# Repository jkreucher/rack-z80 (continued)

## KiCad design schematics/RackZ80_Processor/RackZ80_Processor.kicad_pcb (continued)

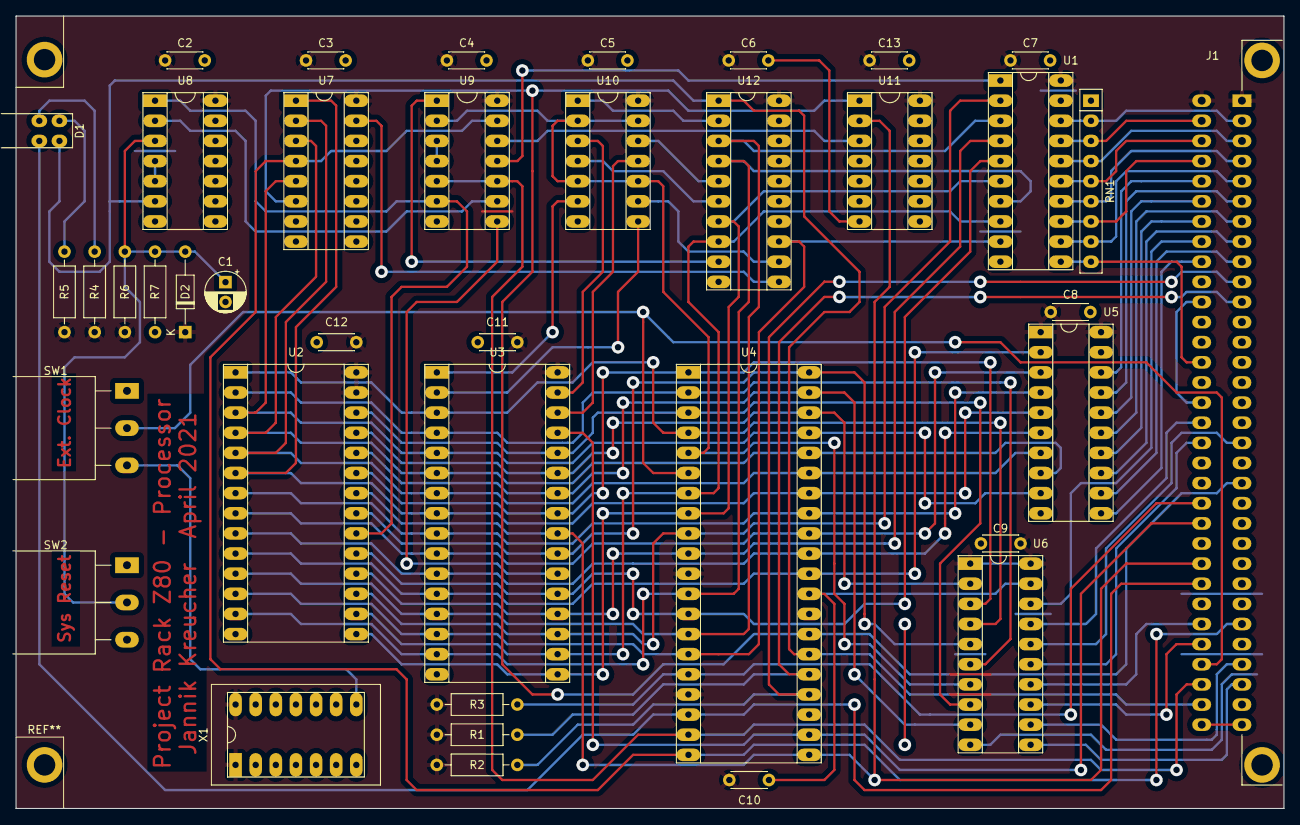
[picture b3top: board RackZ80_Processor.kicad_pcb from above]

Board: 2 copper layers, 160.0 x 100.0 mm, 39 parts (0 on the bottom side), 83 nets.

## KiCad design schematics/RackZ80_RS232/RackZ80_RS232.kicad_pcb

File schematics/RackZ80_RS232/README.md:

# Serial I/O

Copyright 2021 Jannik Kreucher

## Table of Contents
 - [How it works](#how-it-works)
 - [Schematic](#schematic)

## How it works
TODO

## Schematic
The [schematic](documentation/RackZ80_RS232.pdf) exported as pdf. So it is ready to print.

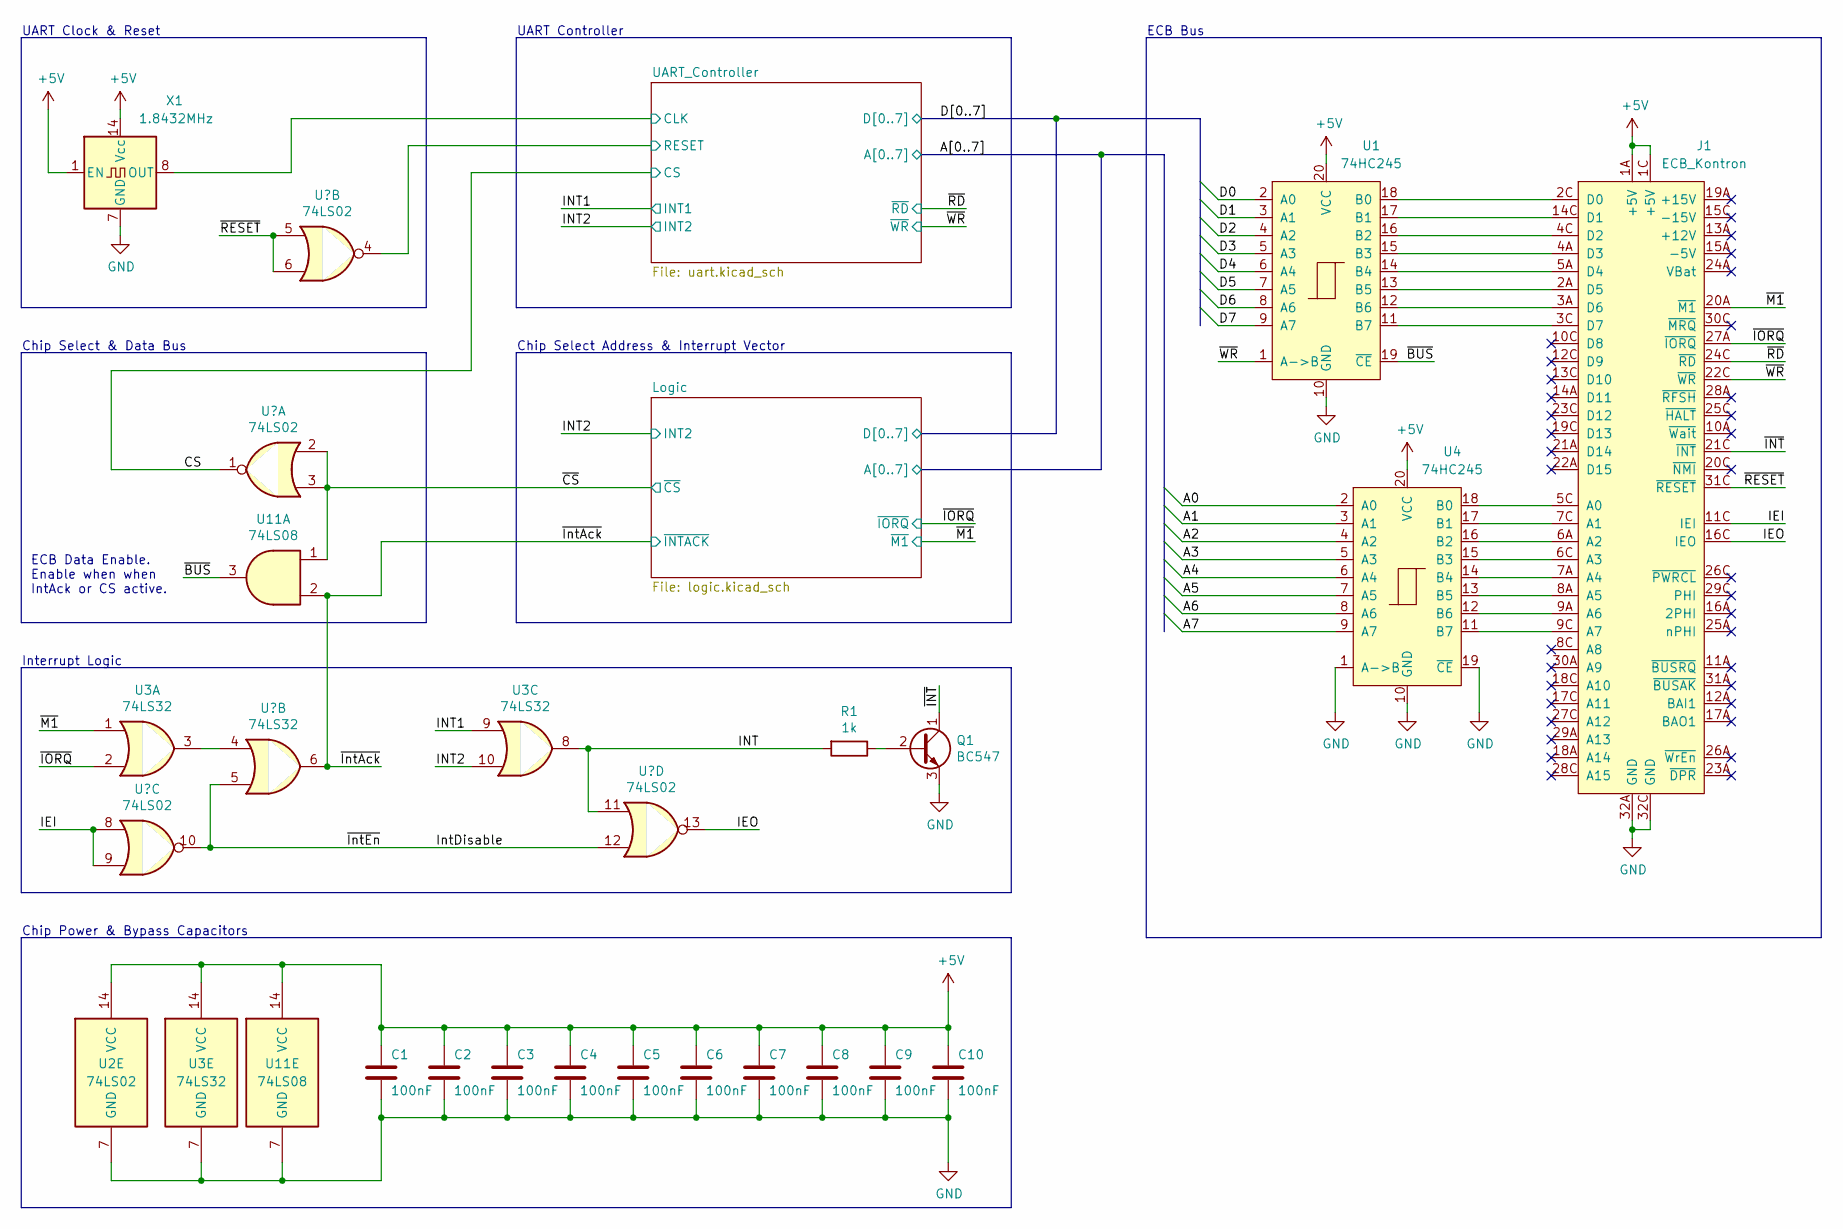
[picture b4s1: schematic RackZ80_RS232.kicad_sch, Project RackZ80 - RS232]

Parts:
C1, C2, C3, C4, C5, C6, C7, C8, C9, C10: 100nF; C_Disc_D4.3mm_W1.9mm_P5.00mm
J1: ECB_Kontron; Eurocard_DIN41612_C64_Male
Q1: BC547; TO-92S_Wide
R1: 1k; R_Axial_DIN0207_L6.3mm_D2.5mm_P10.16mm_Horizontal
U1, U4: 74HC245; DIP-20_Socket
U2: 74LS02; DIP-14_Socket
U3: 74LS32; DIP-14_Socket
U11: 74LS08; DIP-14_Socket
X1: 1.8432MHz; DIP-14_Oscillator_Socket

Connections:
+5V: C1.1, C2.1, C3.1, C4.1, C5.1, C6.1, C7.1, C8.1, C9.1, C10.1, J1.1A (+5V), J1.1C (+5V), U1.20 (VCC), U2.14 (VCC), U3.14 (VCC), U4.20 (VCC), U11.14 (VCC), X1.1 (EN), X1.14 (Vcc); also elsewhere on the board
/A0: U4.2 (A0); also elsewhere on the board
/A1: U4.3 (A1); also elsewhere on the board
/A2: U4.4 (A2); also elsewhere on the board
/A3: U4.5 (A3); also elsewhere on the board
/A4: U4.6 (A4); also elsewhere on the board
/A5: U4.7 (A5); also elsewhere on the board
/A6: U4.8 (A6); also elsewhere on the board
/A7: U4.9 (A7); also elsewhere on the board
/CS: U2.1; also elsewhere on the board
/D0: U1.2 (A0); also elsewhere on the board
/D1: U1.3 (A1); also elsewhere on the board
/D2: U1.4 (A2); also elsewhere on the board
/D3: U1.5 (A3); also elsewhere on the board
/D4: U1.6 (A4); also elsewhere on the board
/D5: U1.7 (A5); also elsewhere on the board
/D6: U1.8 (A6); also elsewhere on the board
/D7: U1.9 (A7); also elsewhere on the board
/IEI: J1.11C (IEI), U2.8, U2.9
/IEO: J1.16C (IEO), U2.13
/INT: R1.2, U2.11, U3.8
/INT1: U3.9; also elsewhere on the board
/INT2: U3.10; also elsewhere on the board
/IntDisable: U2.10, U2.12, U3.5
/UART_Controller/CLK: X1.8 (OUT); also elsewhere on the board
/UART_Controller/RESET: U2.4; also elsewhere on the board
/~BUS: U1.19 (~CE), U11.3
/~CS: U2.2, U2.3, U11.1; also elsewhere on the board
/~INT: J1.21C (~INT), Q1.1 (C)
/~IORQ: J1.27A (~IORQ), U3.2; also elsewhere on the board
/~IntAck: U3.6, U11.2; also elsewhere on the board
/~M1: J1.20A (~M1), U3.1; also elsewhere on the board
/~RD: J1.24C (~RD); also elsewhere on the board
/~RESET: J1.31C (~RESET), U2.5, U2.6
/~WR: J1.22C (~WR), U1.1 (A->B); also elsewhere on the board
GND: C1.2, C2.2, C3.2, C4.2, C5.2, C6.2, C7.2, C8.2, C9.2, C10.2, J1.32A (GND), J1.32C (GND), Q1.3 (E), U1.10 (GND), U2.7 (GND), U3.7 (GND), U4.1 (A->B), U4.10 (GND), U4.19 (~CE), U11.7 (GND), X1.7 (GND); also elsewhere on the board
unnamed: J1.2A (D5), U1.13 (B5)
unnamed: J1.2C (D0), U1.18 (B0)
unnamed: J1.3A (D6), U1.12 (B6)
unnamed: J1.3C (D7), U1.11 (B7)
unnamed: J1.4A (D3), U1.15 (B3)
unnamed: J1.4C (D2), U1.16 (B2)
unnamed: J1.5A (D4), U1.14 (B4)
unnamed: J1.5C (A0), U4.18 (B0)
unnamed: J1.6A (A2), U4.16 (B2)
unnamed: J1.6C (A3), U4.15 (B3)
unnamed: J1.7A (A4), U4.14 (B4)
unnamed: J1.7C (A1), U4.17 (B1)
unnamed: J1.8A (A5), U4.13 (B5)
unnamed: J1.9A (A6), U4.12 (B6)
unnamed: J1.9C (A7), U4.11 (B7)
unnamed: J1.14C (D1), U1.17 (B1)
unnamed: Q1.2 (B), R1.1
unnamed: U3.3, U3.4

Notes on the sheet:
UART Controller
Chip Power & Bypass Capacitors
ECB Bus
Interrupt Logic
Chip Select & Data Bus
Chip Select Address & Interrupt Vector
UART Clock & Reset
ECB Data Enable. Enable when when IntAck or CS active.

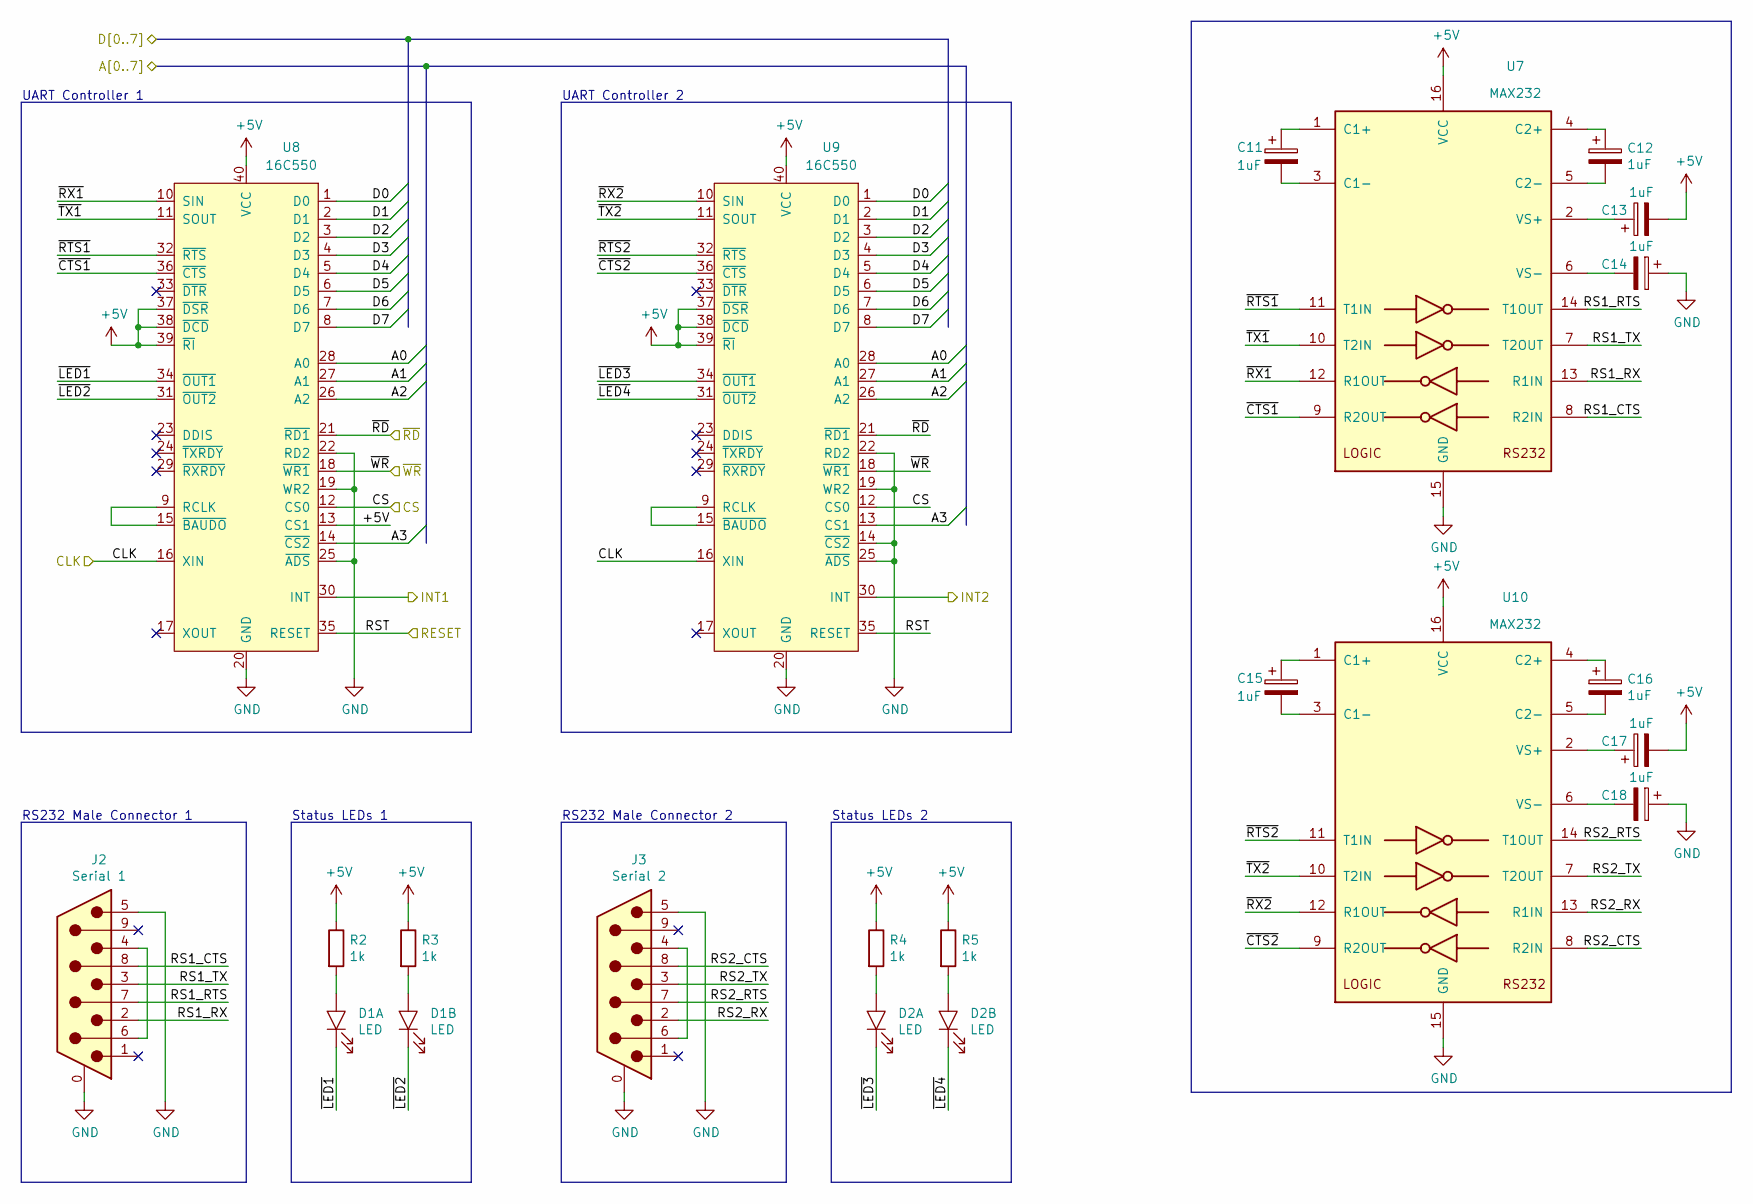
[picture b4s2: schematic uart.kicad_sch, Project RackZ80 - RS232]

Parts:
C11, C12, C13, C14, C15, C16, C17, C18: 1uF; CP_Radial_D5.0mm_P2.00mm
D1, D2: LED; LED_Array_2
J2: Serial 1; DSUB-9_Male_Horizontal_P2.77x2.84mm_EdgePinOffset9.90mm_Hou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
J3: Serial 2; DSUB-9_Male_Horizontal_P2.77x2.84mm_EdgePinOffset9.90mm_Hou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
R2, R3, R4, R5: 1k; R_Axial_DIN0207_L6.3mm_D2.5mm_P10.16mm_Horizontal
U7, U10: MAX232; DIP-16_Socket
U8, U9: 16C550; DIP-40_Socket_Wide

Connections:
+5V: C13.2, C17.2, R2.1, R3.1, R4.1, R5.1, U7.16 (VCC), U8.13 (CS1), U8.37 (~DSR), U8.38 (~DCD), U8.39 (~RI), U8.40 (VCC), U9.37 (~DSR), U9.38 (~DCD), U9.39 (~RI), U9.40 (VCC), U10.16 (VCC); also elsewhere on the board
/A0: U8.28 (A0), U9.28 (A0); also elsewhere on the board
/A1: U8.27 (A1), U9.27 (A1); also elsewhere on the board
/A2: U8.26 (A2), U9.26 (A2); also elsewhere on the board
/A3: U8.14 (~CS2), U9.13 (CS1); also elsewhere on the board
/CS: U8.12 (CS0), U9.12 (CS0); also elsewhere on the board
/D0: U8.1 (D0), U9.1 (D0); also elsewhere on the board
/D1: U8.2 (D1), U9.2 (D1); also elsewhere on the board
/D2: U8.3 (D2), U9.3 (D2); also elsewhere on the board
/D3: U8.4 (D3), U9.4 (D3); also elsewhere on the board
/D4: U8.5 (D4), U9.5 (D4); also elsewhere on the board
/D5: U8.6 (D5), U9.6 (D5); also elsewhere on the board
/D6: U8.7 (D6), U9.7 (D6); also elsewhere on the board
/D7: U8.8 (D7), U9.8 (D7); also elsewhere on the board
/INT1: U8.30 (INT); also elsewhere on the board
/INT2: U9.30 (INT); also elsewhere on the board
/UART_Controller/CLK: U8.16 (XIN), U9.16 (XIN); also elsewhere on the board
/UART_Controller/RESET: U8.35 (RESET), U9.35 (RESET); also elsewhere on the board
/UART_Controller/RS1_CTS: J2.8, U7.8 (R2IN)
/UART_Controller/RS1_RTS: J2.7, U7.14 (T1OUT)
/UART_Controller/RS1_RX: J2.2, U7.13 (R1IN)
/UART_Controller/RS1_TX: J2.3, U7.7 (T2OUT)
/UART_Controller/RS2_CTS: J3.8, U10.8 (R2IN)
/UART_Controller/RS2_RTS: J3.7, U10.14 (T1OUT)
/UART_Controller/RS2_RX: J3.2, U10.13 (R1IN)
/UART_Controller/RS2_TX: J3.3, U10.7 (T2OUT)
/UART_Controller/~CTS1: U7.9 (R2OUT), U8.36 (~CTS)
/UART_Controller/~CTS2: U9.36 (~CTS), U10.9 (R2OUT)
/UART_Controller/~LED1: D1.1 (K), U8.34 (~OUT1)
/UART_Controller/~LED2: D1.3 (K), U8.31 (~OUT2)
/UART_Controller/~LED3: D2.1 (K), U9.34 (~OUT1)
/UART_Controller/~LED4: D2.3 (K), U9.31 (~OUT2)
/UART_Controller/~RTS1: U7.11 (T1IN), U8.32 (~RTS)
/UART_Controller/~RTS2: U9.32 (~RTS), U10.11 (T1IN)
/UART_Controller/~RX1: U7.12 (R1OUT), U8.10 (SIN)
/UART_Controller/~RX2: U9.10 (SIN), U10.12 (R1OUT)
/UART_Controller/~TX1: U7.10 (T2IN), U8.11 (SOUT)
/UART_Controller/~TX2: U9.11 (SOUT), U10.10 (T2IN)
/~RD: U8.21 (~RD1), U9.21 (~RD1); also elsewhere on the board
/~WR: U8.18 (~WR1), U9.18 (~WR1); also elsewhere on the board
GND: C14.1, C18.1, J2.0 (PAD), J2.5, J3.0 (PAD), J3.5, U7.15 (GND), U8.19 (WR2), U8.20 (GND), U8.22 (RD2), U8.25 (~ADS), U9.14 (~CS2), U9.19 (WR2), U9.20 (GND), U9.22 (RD2), U9.25 (~ADS), U10.15 (GND); also elsewhere on the board
unnamed: C11.1, U7.1 (C1+)
unnamed: C11.2, U7.3 (C1-)
unnamed: C12.1, U7.4 (C2+)
unnamed: C12.2, U7.5 (C2-)
unnamed: C13.1, U7.2 (VS+)
unnamed: C14.2, U7.6 (VS-)
unnamed: C15.1, U10.1 (C1+)
unnamed: C15.2, U10.3 (C1-)
unnamed: C16.1, U10.4 (C2+)
unnamed: C16.2, U10.5 (C2-)
unnamed: C17.1, U10.2 (VS+)
unnamed: C18.2, U10.6 (VS-)
unnamed: D1.2 (A), R2.2
unnamed: D1.4 (A), R3.2
unnamed: D2.2 (A), R4.2
unnamed: D2.4 (A), R5.2
unnamed: J2.4, J2.6
unnamed: J3.4, J3.6
unnamed: U8.9 (RCLK), U8.15 (~BAUDO)
unnamed: U9.9 (RCLK), U9.15 (~BAUDO)

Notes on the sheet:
RS232 Male Connector 1
UART Controller 2
Status LEDs 1
RS232 Male Connector 2
Status LEDs 2
UART Controller 1

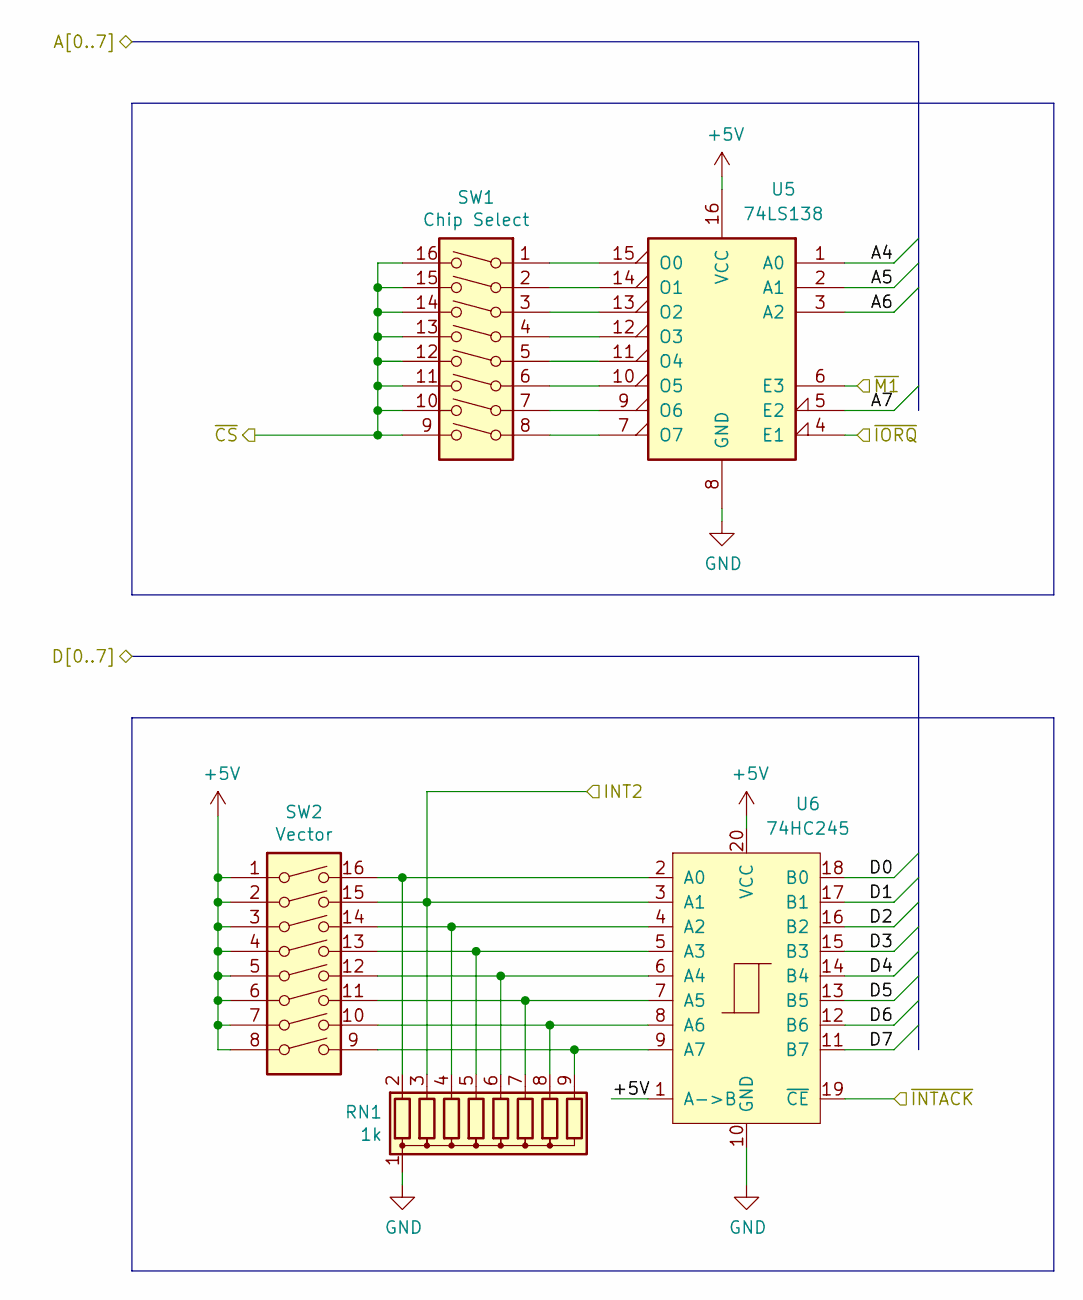
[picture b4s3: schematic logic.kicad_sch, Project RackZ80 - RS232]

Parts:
RN1: 1k; R_Array_SIP9
SW1: Chip Select; SW_DIP_SPSTx08_Slide_9.78x22.5mm_W7.62mm_P2.54mm
SW2: Vector; SW_DIP_SPSTx08_Slide_9.78x22.5mm_W7.62mm_P2.54mm
U5: 74LS138; DIP-16_Socket
U6: 74HC245; DIP-20_Socket

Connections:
+5V: SW2.1, SW2.2, SW2.3, SW2.4, SW2.5, SW2.6, SW2.7, SW2.8, U5.16 (VCC), U6.1 (A->B), U6.20 (VCC); also elsewhere on the board
/A4: U5.1 (A0); also elsewhere on the board
/A5: U5.2 (A1); also elsewhere on the board
/A6: U5.3 (A2); also elsewhere on the board
/A7: U5.5 (E2); also elsewhere on the board
/D0: U6.18 (B0); also elsewhere on the board
/D1: U6.17 (B1); also elsewhere on the board
/D2: U6.16 (B2); also elsewhere on the board
/D3: U6.15 (B3); also elsewhere on the board
/D4: U6.14 (B4); also elsewhere on the board
/D5: U6.13 (B5); also elsewhere on the board
/D6: U6.12 (B6); also elsewhere on the board
/D7: U6.11 (B7); also elsewhere on the board
/INT2: RN1.3 (R2), SW2.15, U6.3 (A1); also elsewhere on the board
/~CS: SW1.9, SW1.10, SW1.11, SW1.12, SW1.13, SW1.14, SW1.15, SW1.16; also elsewhere on the board
/~IORQ: U5.4 (E1); also elsewhere on the board
/~IntAck: U6.19 (~CE); also elsewhere on the board
/~M1: U5.6 (E3); also elsewhere on the board
GND: RN1.1 (common), U5.8 (GND), U6.10 (GND); also elsewhere on the board
unnamed: RN1.2 (R1), SW2.16, U6.2 (A0)
unnamed: RN1.4 (R3), SW2.14, U6.4 (A2)
unnamed: RN1.5 (R4), SW2.13, U6.5 (A3)
unnamed: RN1.6 (R5), SW2.12, U6.6 (A4)
unnamed: RN1.7 (R6), SW2.11, U6.7 (A5)
unnamed: RN1.8 (R7), SW2.10, U6.8 (A6)
unnamed: RN1.9 (R8), SW2.9, U6.9 (A7)
unnamed: SW1.1, U5.15 (O0)
unnamed: SW1.2, U5.14 (O1)
unnamed: SW1.3, U5.13 (O2)
unnamed: SW1.4, U5.12 (O3)
unnamed: SW1.5, U5.11 (O4)
unnamed: SW1.6, U5.10 (O5)
unnamed: SW1.7, U5.9 (O6)
unnamed: SW1.8, U5.7 (O7)

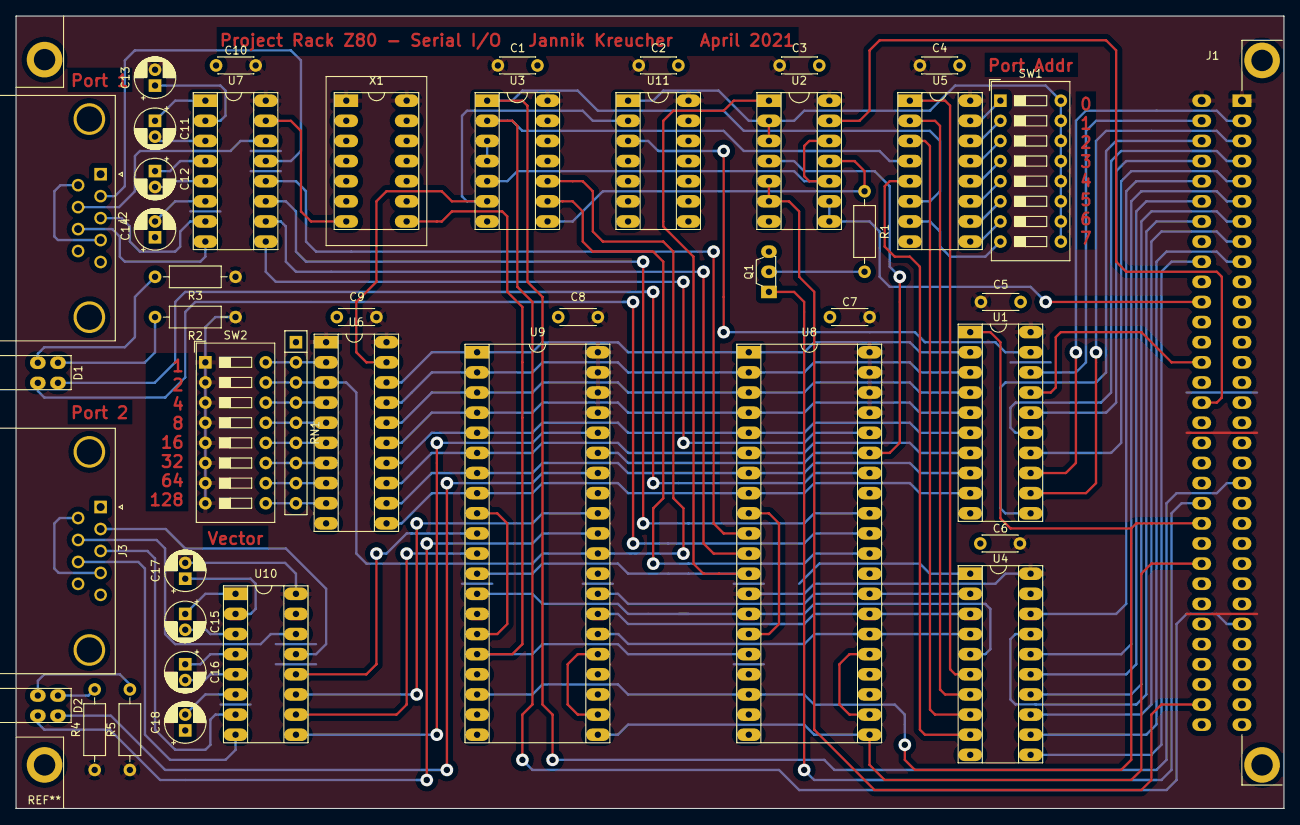
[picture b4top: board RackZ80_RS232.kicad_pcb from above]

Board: 2 copper layers, 160.0 x 100.0 mm, 44 parts (0 on the bottom side), 109 nets.

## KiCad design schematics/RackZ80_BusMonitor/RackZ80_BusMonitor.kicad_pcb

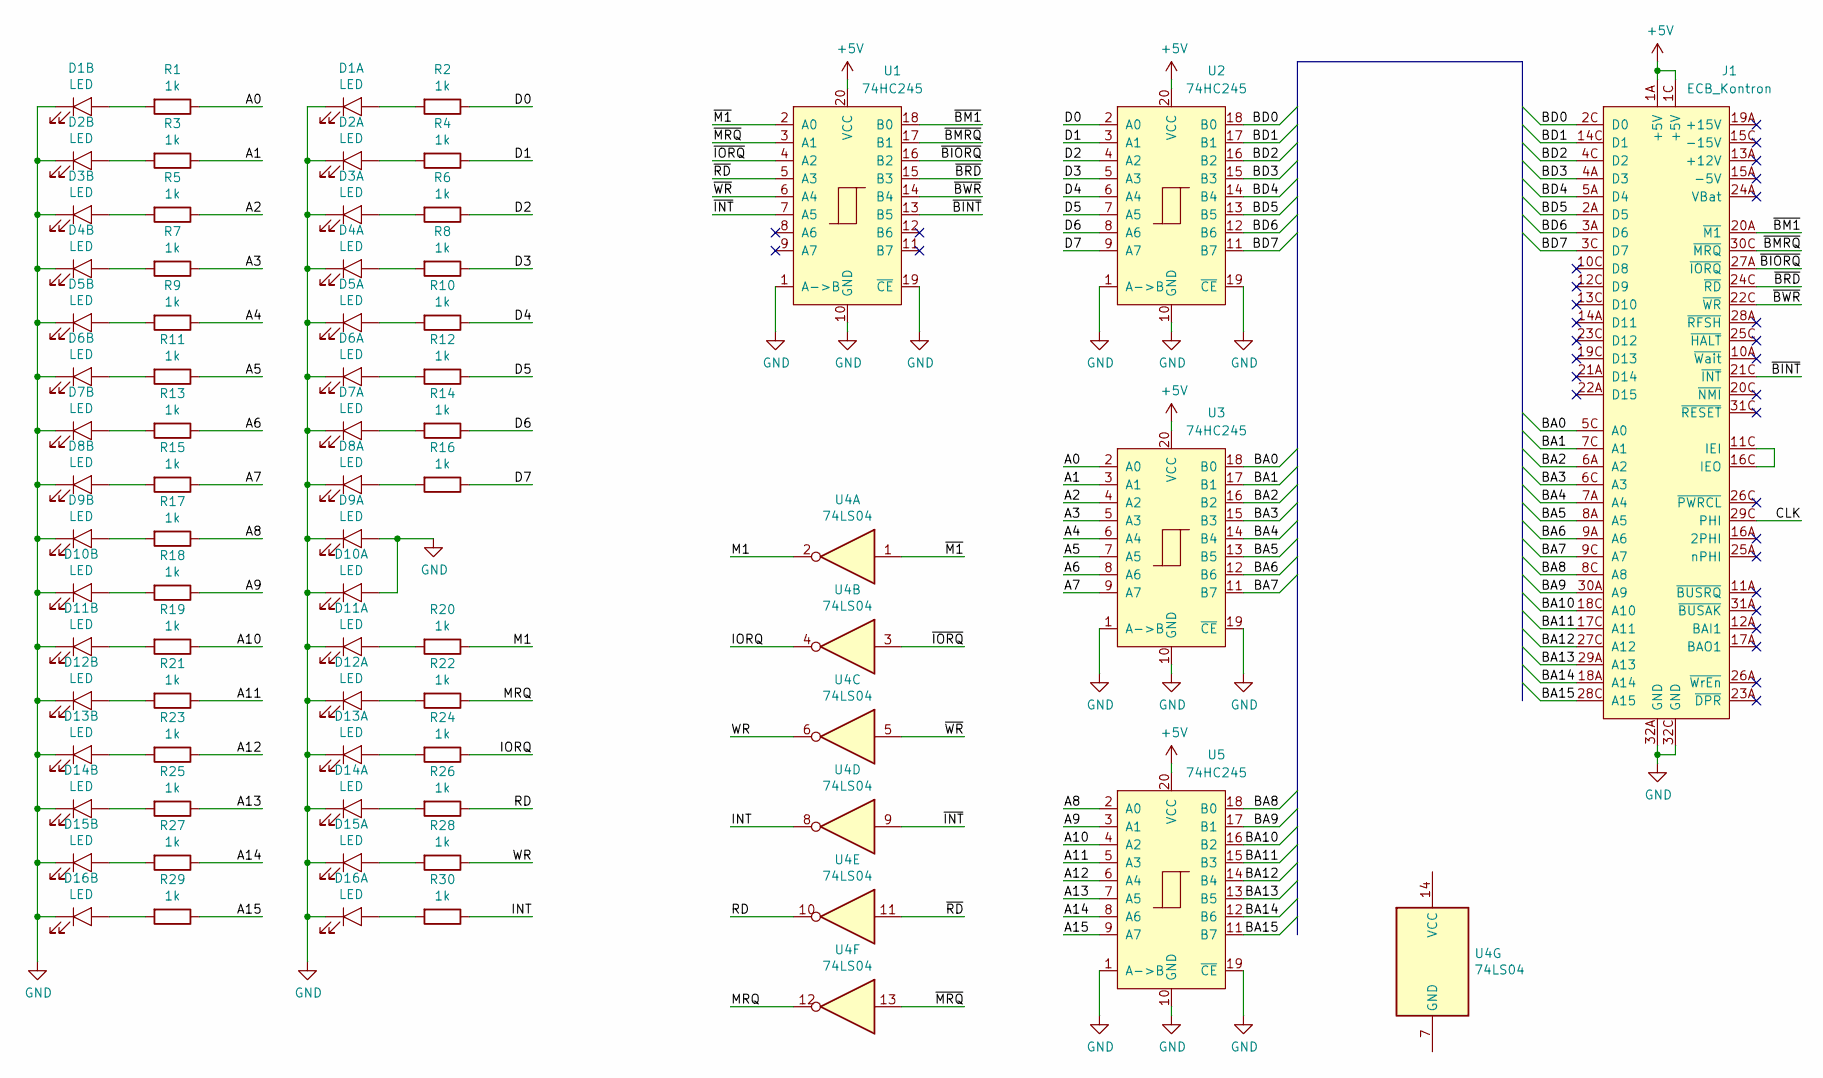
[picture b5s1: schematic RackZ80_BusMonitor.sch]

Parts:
D1, D2, D3, D4, D5, D6, D7, D8, D9, D10, D11, D12, D13, D14, D15, D16: LED; LED_Array_2
J1: ECB_Kontron; Eurocard_DIN41612_C64_Male
R1, R2, R3, R4, R5, R6, R7, R8, R9, R10, R11, R12, R13, R14, R15, R16, R17, R18, R19, R20, R21, R22, R23, R24, R25, R26, R27, R28, R29, R30: 1k; R_Axial_DIN0207_L6.3mm_D2.5mm_P10.16mm_Horizontal
U1, U2, U3, U5: 74HC245; DIP-20_Socket
U4: 74LS04; DIP-14_Socket

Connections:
+5V: J1.1A (+5V), J1.1C (+5V), U1.20 (VCC), U2.20 (VCC), U3.20 (VCC), U5.20 (VCC)
/A0: R1.1, U3.2 (A0)
/A1: R3.1, U3.3 (A1)
/A2: R5.1, U3.4 (A2)
/A3: R7.1, U3.5 (A3)
/A4: R9.1, U3.6 (A4)
/A5: R11.1, U3.7 (A5)
/A6: R13.1, U3.8 (A6)
/A7: R15.1, U3.9 (A7)
/A8: R17.1, U5.2 (A0)
/A9: R18.1, U5.3 (A1)
/A10: R19.1, U5.4 (A2)
/A11: R21.1, U5.5 (A3)
/A12: R23.1, U5.6 (A4)
/A13: R25.1, U5.7 (A5)
/A14: R27.1, U5.8 (A6)
/A15: R29.1, U5.9 (A7)
/BA0: J1.5C (A0), U3.18 (B0)
/BA1: J1.7C (A1), U3.17 (B1)
/BA2: J1.6A (A2), U3.16 (B2)
/BA3: J1.6C (A3), U3.15 (B3)
/BA4: J1.7A (A4), U3.14 (B4)
/BA5: J1.8A (A5), U3.13 (B5)
/BA6: J1.9A (A6), U3.12 (B6)
/BA7: J1.9C (A7), U3.11 (B7)
/BA8: J1.8C (A8), U5.18 (B0)
/BA9: J1.30A (A9), U5.17 (B1)
/BA10: J1.18C (A10), U5.16 (B2)
/BA11: J1.17C (A11), U5.15 (B3)
/BA12: J1.27C (A12), U5.14 (B4)
/BA13: J1.29A (A13), U5.13 (B5)
/BA14: J1.18A (A14), U5.12 (B6)
/BA15: J1.28C (A15), U5.11 (B7)
/BD0: J1.2C (D0), U2.18 (B0)
/BD1: J1.14C (D1), U2.17 (B1)
/BD2: J1.4C (D2), U2.16 (B2)
/BD3: J1.4A (D3), U2.15 (B3)
/BD4: J1.5A (D4), U2.14 (B4)
/BD5: J1.2A (D5), U2.13 (B5)
/BD6: J1.3A (D6), U2.12 (B6)
/BD7: J1.3C (D7), U2.11 (B7)
/CLK: J1.29C (PHI)
/D0: R2.1, U2.2 (A0)
/D1: R4.1, U2.3 (A1)
/D2: R6.1, U2.4 (A2)
/D3: R8.1, U2.5 (A3)
/D4: R10.1, U2.6 (A4)
/D5: R12.1, U2.7 (A5)
/D6: R14.1, U2.8 (A6)
/D7: R16.1, U2.9 (A7)
/INT: R30.1, U4.8
/IORQ: R24.1, U4.4
/M1: R20.1, U4.2
/MRQ: R22.1, U4.12
/RD: R26.1, U4.10
/WR: R28.1, U4.6
/~BINT: J1.21C (~INT), U1.13 (B5)
/~BIORQ: J1.27A (~IORQ), U1.16 (B2)
/~BM1: J1.20A (~M1), U1.18 (B0)
/~BMRQ: J1.30C (~MRQ), U1.17 (B1)
/~BRD: J1.24C (~RD), U1.15 (B3)
/~BWR: J1.22C (~WR), U1.14 (B4)
/~INT: U1.7 (A5), U4.9
/~IORQ: U1.4 (A2), U4.3
/~M1: U1.2 (A0), U4.1
/~MRQ: U1.3 (A1), U4.13
/~RD: U1.5 (A3), U4.11
/~WR: U1.6 (A4), U4.5
GND: D1.1 (K), D1.3 (K), D2.1 (K), D2.3 (K), D3.1 (K), D3.3 (K), D4.1 (K), D4.3 (K), D5.1 (K), D5.3 (K), D6.1 (K), D6.3 (K), D7.1 (K), D7.3 (K), D8.1 (K), D8.3 (K), D9.1 (K), D9.2 (A), D9.3 (K), D10.1 (K), D10.2 (A), D10.3 (K), D11.1 (K), D11.3 (K), D12.1 (K), D12.3 (K), D13.1 (K), D13.3 (K), D14.1 (K), D14.3 (K), D15.1 (K), D15.3 (K), D16.1 (K), D16.3 (K), J1.32A (GND), J1.32C (GND), U1.1 (A->B), U1.10 (GND), U1.19 (~CE), U2.1 (A->B), U2.10 (GND), U2.19 (~CE), U3.1 (A->B), U3.10 (GND), U3.19 (~CE), U5.1 (A->B), U5.10 (GND), U5.19 (~CE)
unnamed: D1.2 (A), R2.2
unnamed: D1.4 (A), R1.2
unnamed: D2.2 (A), R4.2
unnamed: D2.4 (A), R3.2
unnamed: D3.2 (A), R6.2
unnamed: D3.4 (A), R5.2
unnamed: D4.2 (A), R8.2
unnamed: D4.4 (A), R7.2
unnamed: D5.2 (A), R10.2
unnamed: D5.4 (A), R9.2
unnamed: D6.2 (A), R12.2
unnamed: D6.4 (A), R11.2
unnamed: D7.2 (A), R14.2
unnamed: D7.4 (A), R13.2
unnamed: D8.2 (A), R16.2
unnamed: D8.4 (A), R15.2
unnamed: D9.4 (A), R17.2
unnamed: D10.4 (A), R18.2
unnamed: D11.2 (A), R20.2
unnamed: D11.4 (A), R19.2
unnamed: D12.2 (A), R22.2
unnamed: D12.4 (A), R21.2
unnamed: D13.2 (A), R24.2
unnamed: D13.4 (A), R23.2
unnamed: D14.2 (A), R26.2
unnamed: D14.4 (A), R25.2
unnamed: D15.2 (A), R28.2
unnamed: D15.4 (A), R27.2
unnamed: D16.2 (A), R30.2
unnamed: D16.4 (A), R29.2
unnamed: J1.11C (IEI), J1.16C (IEO)

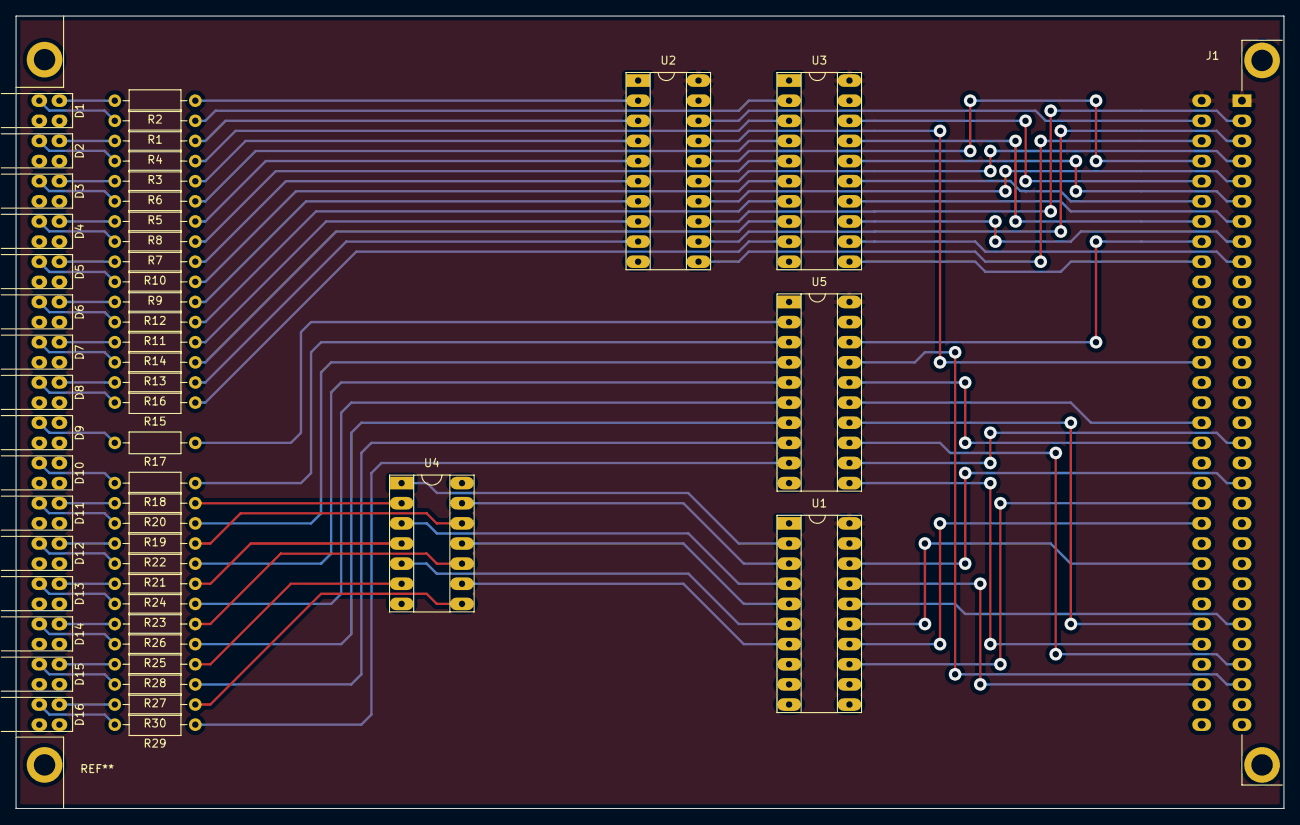
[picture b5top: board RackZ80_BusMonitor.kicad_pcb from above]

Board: 2 copper layers, 160.0 x 100.0 mm, 52 parts (0 on the bottom side), 99 nets.

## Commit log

2021-03-07 main readme addition
2021-03-07 readme folder names
2021-03-07 readme fix
2021-03-08 processor schematic 3d models
2021-03-08 add kontron ecb symbol
2021-03-14 Breadboard Prototype
2021-04-16 schematics update
2021-07-13 new picture
2021-07-13 new pictures
2021-07-13 picture in readme
2022-03-27 create code folder
2022-03-27 added first test files
2023-02-02 sdcc test template
2023-02-02 adcc template fix
2023-11-04 uart demo code fixed
2023-11-05 migrated kicad 5 to kicad 7
2023-11-14 simple monitor code and power supply module
2023-11-15 monitor code
2023-11-15 monitor send bytes script
2023-11-16 monitor code: better memory dump
